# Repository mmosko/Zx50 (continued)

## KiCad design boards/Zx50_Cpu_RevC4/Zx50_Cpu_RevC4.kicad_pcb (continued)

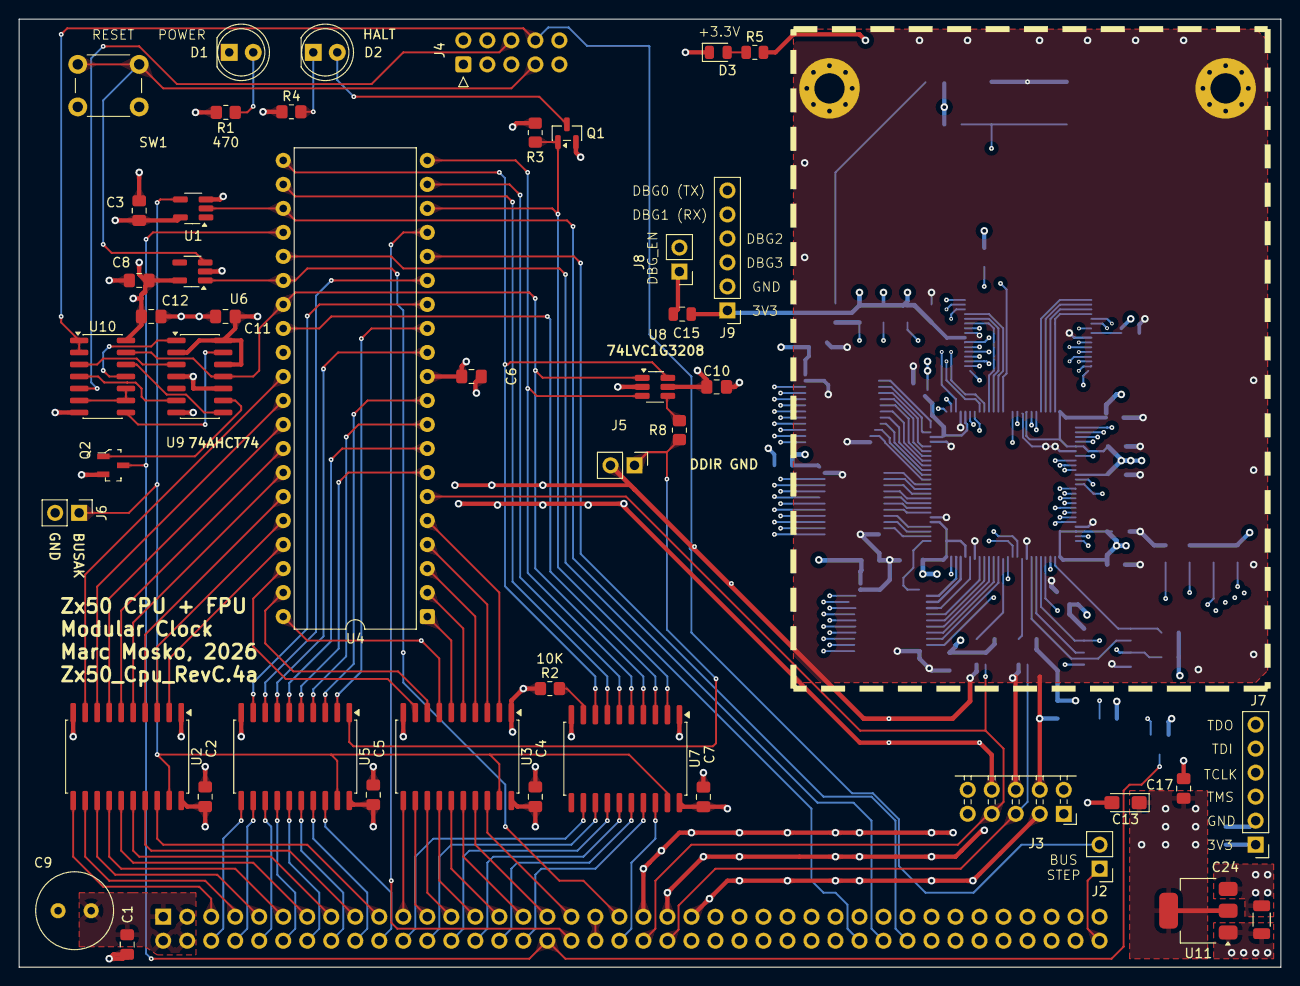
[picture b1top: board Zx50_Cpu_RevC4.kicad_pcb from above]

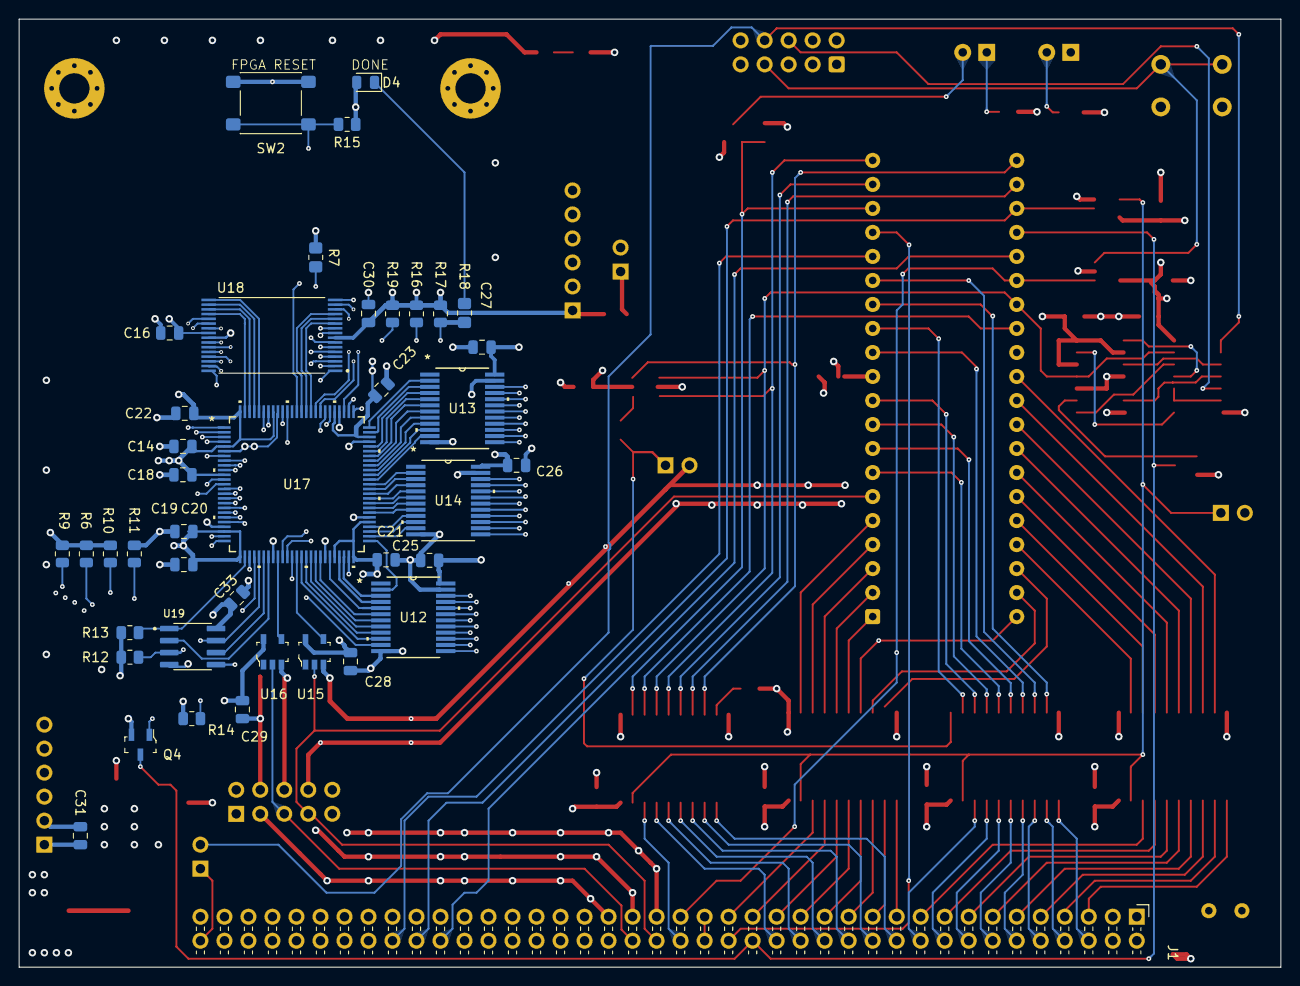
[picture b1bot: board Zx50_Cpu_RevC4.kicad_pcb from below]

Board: 6 copper layers, 133.5 x 100.3 mm, 88 parts (41 on the bottom side), 174 nets.

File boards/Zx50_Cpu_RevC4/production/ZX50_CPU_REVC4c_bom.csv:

Designator,Footprint,Quantity,Value,LCSC Part #
"C1, C10, C11, C12, C2, C3, C4, C5, C6, C7, C8",0805,11,0.1uF,C1525
C13,CP_EIA-3216-10_Kemet-I_HandSolder,1,10u,C7171
"C14, C15, C16, C18, C19, C20, C21, C22, C23, C25, C26, C27, C28, C29, C30, C31",0805,16,100nF,C28233
C17,0805,1,100n,C1525
C24,1206,1,10u,C7171
C33,0805,1,100n,C49678
C9,C_Radial_D8.0mm_H7.0mm_P3.50mm,1,100uF,
D1,LED_D5.0mm,1,PWR,
D2,LED_D5.0mm,1,HALT,
D4,0805,1,DONE,C2297
J1,PinHeader_2x40_P2.54mm_Horizontal_Edge,1,Zx50_EdgeConnector,
J2,PinHeader_1x02_P2.54mm_Vertical,1,STEP_N,
J3,PinSocket_2x05_P2.54mm_Horizontal,1,Clock Mezzanine,
J4,IDC-Header_2x05_P2.54mm_Horizontal_Edge,1,Front Panel,
J5,PinHeader_1x02_P2.54mm_Vertical,1,TP_D_DIR,
J6,PinHeader_1x02_P2.54mm_Vertical,1,TP_BUSAK,
J7,PinHeader_1x06_P2.54mm_Vertical,1,JTAG,
J8,PinHeader_1x02_P2.54mm_Vertical,1,DBG_EN,
J9,PinHeader_1x06_P2.54mm_Vertical,1,DEBUG,
Q1,SOT-23,1,BSS84,
"Q2, Q4",SOT-23-3,2,2N7002-7-F,C8545
"R1, R4",0805,2,470,C17710
"R10, R11, R15, R16, R17, R19, R6, R9",0805,8,4k7,C17713
"R12, R13, R14, R2, R7",0805,5,10k,C17414
R3,0805,1,47K,C17713
R8,0805,1,33R,C17634
SW1,SW_PUSH_6mm_H7.3mm,1,RESET,
SW2,SW_SPST_PTS645Sx43SMTR92,1,RESET,
U1,SOT-23-5_HandSoldering,1,74AHC1G14,
U10,SOIC-14_3.9x8.7mm_P1.27mm,1,74ACHT132,
U11,SOT-223-3_TabPin2,1,AMS1117-3.3,C6186
"U12, U13, U14",DB24,3,74CBTD3861,C11617
"U15, U16",SOT-753,2,74LVC1G17,C7836
U17,TQFP100_LAT,1,LCMXO2-2000HC-4TG100I,C1521620
U18,SOP50P1400X120-32N,1,IS61WV1288EEBLL-10HLI,C1349956
U19,SOIC127P600X88-8N,1,IS25LP080D-JNLE-TR,C521286
"U2, U3, U5, U7",SOIC-20W_7.5x12.8mm_P1.27mm,4,SN74ABT245BN,
U4,DIP-40_W15.24mm,1,Z84C00xxP,
U6,SOT-23-5_HandSoldering,1,MCP1316MT-46LE/OT,
U8,SOT-23-6_Handsoldering,1,74LVC1G3208,
U9,SOIC-14_3.9x8.7mm_P1.27mm,1,SN74AHCT74DRG4,

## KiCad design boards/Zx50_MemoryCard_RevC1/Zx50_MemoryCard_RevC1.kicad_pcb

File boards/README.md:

# Zx50 Project Architecture Context

## Overview

The Zx50 is a custom 8-slot, passive backplane Z80 computer. It uses a "Shadow Bus" architecture where a Raspberry Pi Pico can take over the bus via DMA (~BUSRQ / ~BUSAK) to load RAM, debug, and monitor the system.

## Core Rules & Hardware

* Backplane: 8 slots. Fully terminated with 10K SIP pull-up resistors on Address, Data, and Control lines. Includes an ~IEI/~IEO interrupt daisy chain and heavy bulk capacitance (1000µF).

* CPU: Z80 running at 8 to 10 MHz.

* Clock System: A dedicated Clock Mezzanine board that generates a 40 MHz Master Clock (MCLK) for the Pi Picos, and uses a 74HC393 to divide it down to a 10 MHz ZCLK for the Z80. It uses an async-request latch system (1G79, 1G08, 1G32) to perfectly sync the CPU clock stopping/stepping with the Pi Pico's requests, ensuring no runt pulses.

* Logic Families: * 74AHCT (specifically 74AHCT244 and 74AHCT245) are used for bus transceivers to provide the strong ±8mA current needed to drive the backplane.

* Standard 74HC / 74AHC logic is used for local onboard glue logic.

* System Reset: Handled by an MCP1316M-46LE/OT Open-Drain Supervisor IC on the CPU card. It provides a ~200ms reset timeout to allow the backplane capacitors to charge and the Pi Pico bootloaders to initialize before the Z80 wakes up.

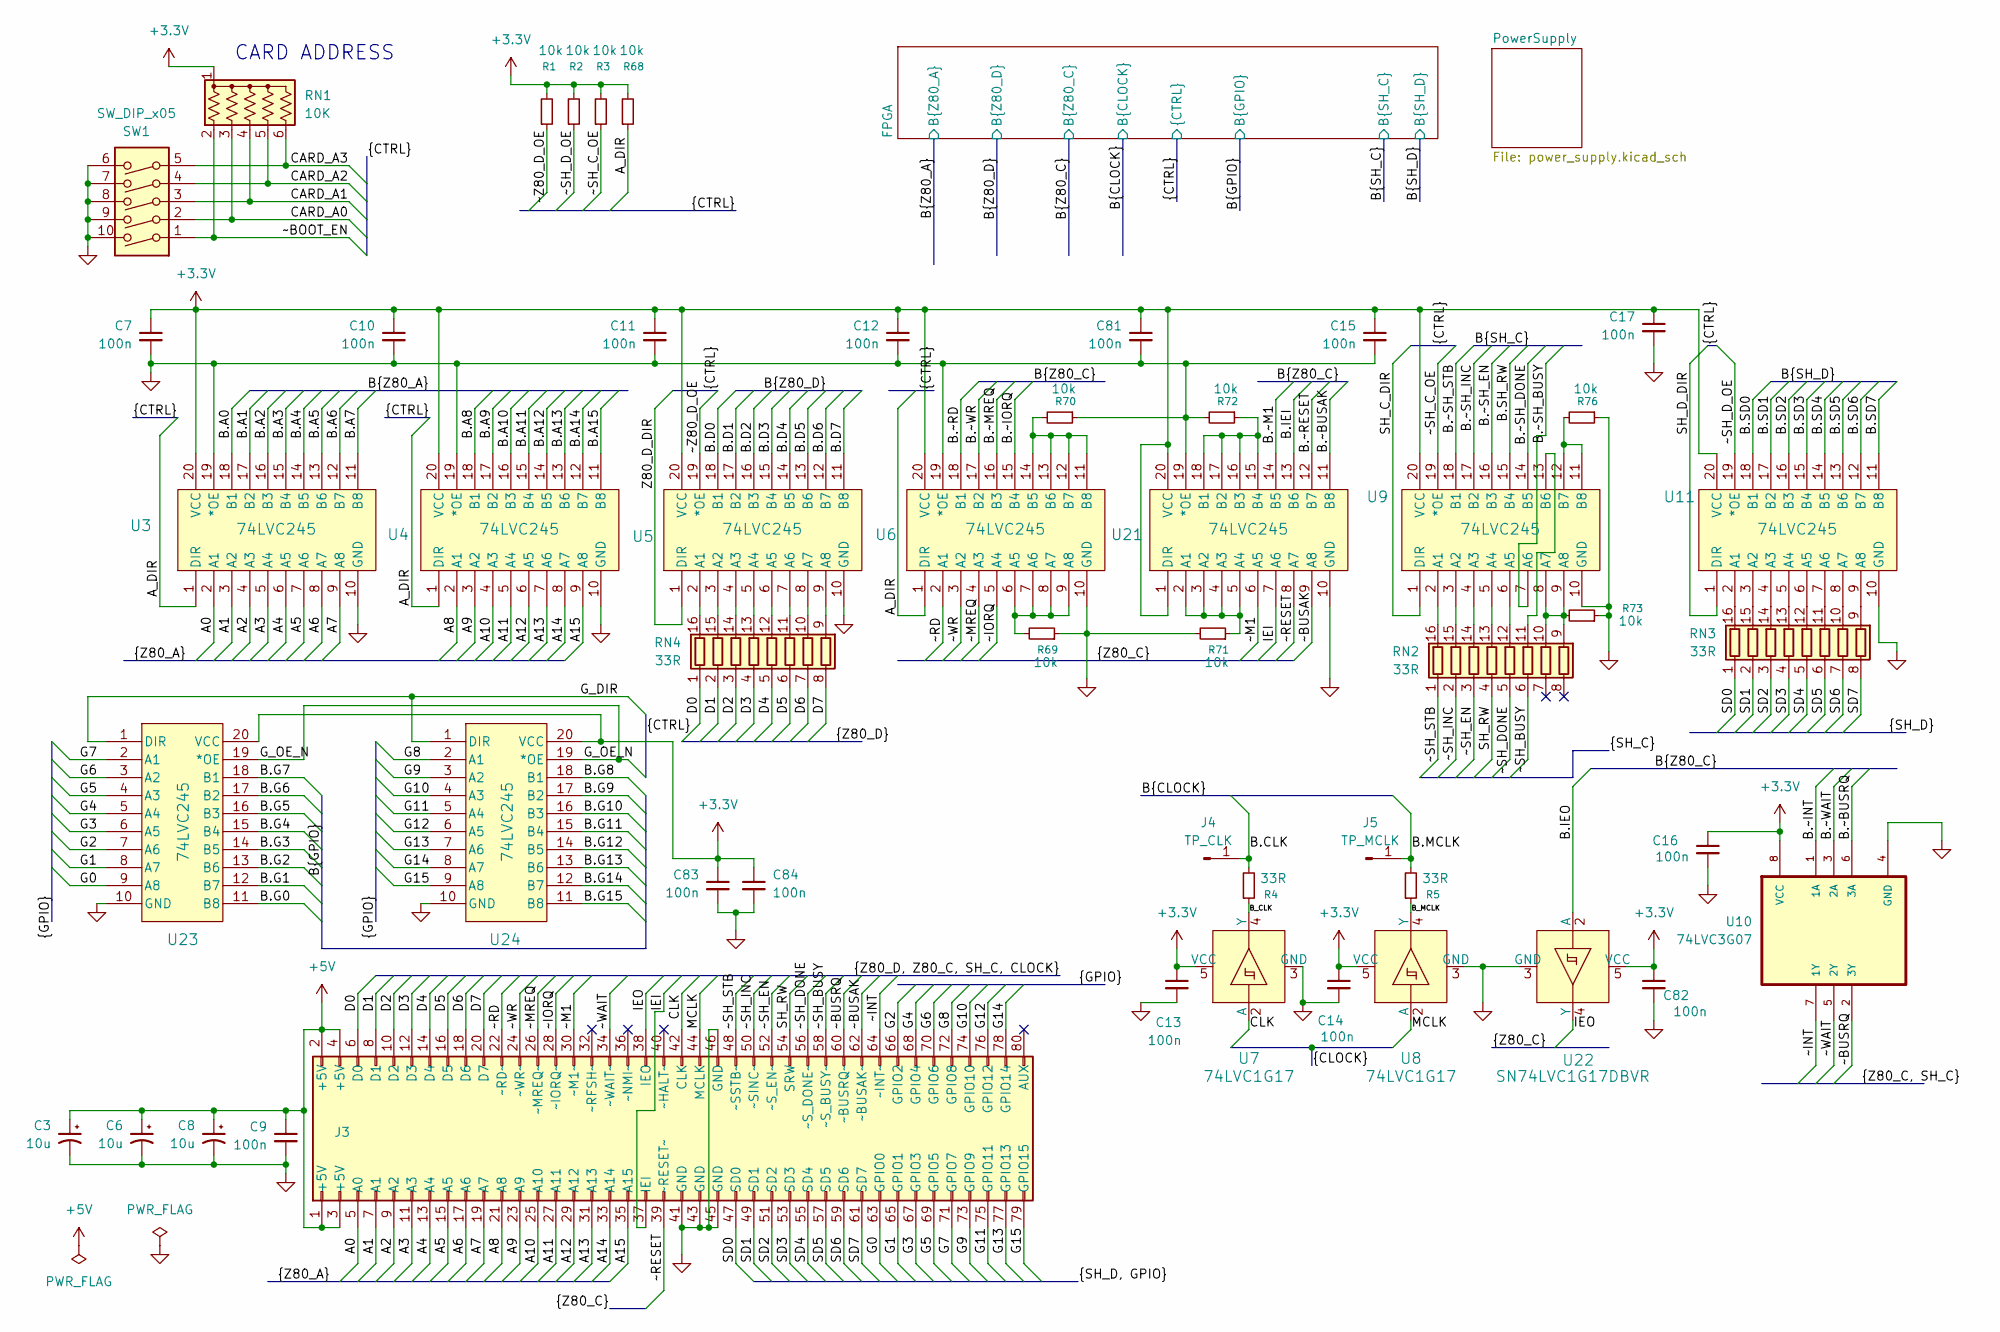
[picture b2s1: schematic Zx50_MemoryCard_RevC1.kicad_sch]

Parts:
C3, C6, C8: 10u; C_1206_3216Metric; MFG PN AVX TAJA106K016RNJ Tantalinium; LCSC C7171
C7, C9, C10, C11, C12, C13, C14, C15, C16, C17, C81, C82, C83, C84: 100n; C_0402_1005Metric; LCSC C1525
J3: Zx50_EdgeConnector; PinSocket_2x40_P2.54mm_Horizontal_Edge; DigiKey_PN 2057-PH2RA-80-UA-ND
J4: TP_CLK; PinHeader_1x01_P2.54mm_Vertical
J5: TP_MCLK; PinHeader_1x01_P2.54mm_Vertical
R1, R2, R3, R68, R69, R70, R71, R72, R73, R76: 10k; R_0805_2012Metric; MFG_PN 0805W8F1002T5E; LCSC C17414
R4, R5: 33R; R_0603_1608Metric; MFG_PN 0603WAF330JT5E; LCSC C23140
RN1: 10K; R_Array_SIP6; LCSC 4606X-AP1-103LF
RN2, RN3, RN4: 33R; R_Array_Convex_8x0602; LCSC C422182
SW1: SW_DIP_x05; SW_DIP_SPSTx05_Slide_9.78x14.88mm_W7.62mm_P2.54mm; LCSC 208-5
U3, U4, U5, U6, U9, U11, U21, U23, U24: 74LVC245; TSSOP-20_4.4x6.5mm_P0.65mm; MFG_PART SN74LVC245APWR; LCSC C7848
U7, U8: 74LVC1G17; SOT-753; MPN SN74LVC1G17DBVR; Digi-Key_PN 296-11933-1-ND
U10: 74LVC3G07; VSSOP-8_2.3x2mm_P0.5mm; MFG_PN SN74LVC3G07DCUR; LCSC C131955
U22: SN74LVC1G17DBVR; SOT-753; MPN SN74LVC1G17DBVR; Digi-Key_PN 296-11933-1-ND

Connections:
+3.3V: C7.1, C10.1, C11.1, C12.1, C13.1, C14.1, C15.1, C16.1, C17.1, C81.1, C82.1, C83.1, C84.1, R1.2, R2.2, R3.2, R68.2, RN1.1 (common), U3.20 (VCC), U4.20 (VCC), U5.20 (VCC), U6.20 (VCC), U7.5 (VCC), U8.5 (VCC), U9.20 (VCC), U10.8 (VCC), U11.20 (VCC), U21.1 (DIR), U21.20 (VCC), U22.5 (VCC), U23.20 (VCC), U24.20 (VCC); also elsewhere on the board
+5V: C3.1, C6.1, C8.1, C9.1, J3.1 (+5V), J3.2 (+5V), J3.3 (+5V), J3.4 (+5V); also elsewhere on the board
/A0: J3.5 (A0), U3.2 (A1)
/A1: J3.7 (A1), U3.3 (A2)
/A2: J3.9 (A2), U3.4 (A3)
/A3: J3.11 (A3), U3.5 (A4)
/A4: J3.13 (A4), U3.6 (A5)
/A5: J3.15 (A5), U3.7 (A6)
/A6: J3.17 (A6), U3.8 (A7)
/A7: J3.19 (A7), U3.9 (A8)
/A8: J3.21 (A8), U4.2 (A1)
/A9: J3.23 (A9), U4.3 (A2)
/A10: J3.25 (A10), U4.4 (A3)
/A11: J3.27 (A11), U4.5 (A4)
/A12: J3.29 (A12), U4.6 (A5)
/A13: J3.31 (A13), U4.7 (A6)
/A14: J3.33 (A14), U4.8 (A7)
/A15: J3.35 (A15), U4.9 (A8)
/A_DIR: R68.1, U3.1 (DIR), U4.1 (DIR), U6.1 (DIR); also elsewhere on the board
/B.A0: U3.18 (B1); also elsewhere on the board
/B.A1: U3.17 (B2); also elsewhere on the board
/B.A2: U3.16 (B3); also elsewhere on the board
/B.A3: U3.15 (B4); also elsewhere on the board
/B.A4: U3.14 (B5); also elsewhere on the board
/B.A5: U3.13 (B6); also elsewhere on the board
/B.A6: U3.12 (B7); also elsewhere on the board
/B.A7: U3.11 (B8); also elsewhere on the board
/B.A8: U4.18 (B1); also elsewhere on the board
/B.A9: U4.17 (B2); also elsewhere on the board
/B.A10: U4.16 (B3); also elsewhere on the board
/B.A11: U4.15 (B4); also elsewhere on the board
/B.A12: U4.14 (B5); also elsewhere on the board
/B.A13: U4.13 (B6); also elsewhere on the board
/B.A14: U4.12 (B7); also elsewhere on the board
/B.A15: U4.11 (B8); also elsewhere on the board
/B.CLK: J4.1, R4.2; also elsewhere on the board
/B.D0: U5.18 (B1); also elsewhere on the board
/B.D1: U5.17 (B2); also elsewhere on the board
/B.D2: U5.16 (B3); also elsewhere on the board
/B.D3: U5.15 (B4); also elsewhere on the board
/B.D4: U5.14 (B5); also elsewhere on the board
/B.D5: U5.13 (B6); also elsewhere on the board
/B.D6: U5.12 (B7); also elsewhere on the board
/B.D7: U5.11 (B8); also elsewhere on the board
/B.G0: U23.11 (B8); also elsewhere on the board
/B.G1: U23.12 (B7); also elsewhere on the board
/B.G2: U23.13 (B6); also elsewhere on the board
/B.G3: U23.14 (B5); also elsewhere on the board
/B.G4: U23.15 (B4); also elsewhere on the board
/B.G5: U23.16 (B3); also elsewhere on the board
/B.G6: U23.17 (B2); also elsewhere on the board
/B.G7: U23.18 (B1); also elsewhere on the board
/B.G8: U24.18 (B1); also elsewhere on the board
/B.G9: U24.17 (B2); also elsewhere on the board
/B.G10: U24.16 (B3); also elsewhere on the board
/B.G11: U24.15 (B4); also elsewhere on the board
/B.G12: U24.14 (B5); also elsewhere on the board
/B.G13: U24.13 (B6); also elsewhere on the board
/B.G14: U24.12 (B7); also elsewhere on the board
/B.G15: U24.11 (B8); also elsewhere on the board
/B.IEI: U21.13 (B6); also elsewhere on the board
/B.IEO: U22.2 (A); also elsewhere on the board
/B.MCLK: J5.1, R5.2; also elsewhere on the board
/B.SD0: U11.18 (B1); also elsewhere on the board
/B.SD1: U11.17 (B2); also elsewhere on the board
/B.SD2: U11.16 (B3); also elsewhere on the board
/B.SD3: U11.15 (B4); also elsewhere on the board
/B.SD4: U11.14 (B5); also elsewhere on the board
/B.SD5: U11.13 (B6); also elsewhere on the board
/B.SD6: U11.12 (B7); also elsewhere on the board
/B.SD7: U11.11 (B8); also elsewhere on the board
/B.SH_RW: U9.15 (B4); also elsewhere on the board
/B.~BUSAK: U21.11 (B8); also elsewhere on the board
/B.~BUSRQ: U10.6 (3A); also elsewhere on the board
/B.~INT: U10.1 (1A); also elsewhere on the board
/B.~IORQ: U6.15 (B4); also elsewhere on the board
/B.~M1: U21.14 (B5); also elsewhere on the board
/B.~MREQ: U6.16 (B3); also elsewhere on the board
/B.~RD: U6.18 (B1); also elsewhere on the board
/B.~RESET: U21.12 (B7); also elsewhere on the board
/B.~SH_BUSY: U9.7 (A6); also elsewhere on the board
/B.~SH_DONE: U9.14 (B5); also elsewhere on the board
/B.~SH_EN: U9.16 (B3); also elsewhere on the board
/B.~SH_INC: U9.17 (B2); also elsewhere on the board
/B.~SH_STB: U9.18 (B1); also elsewhere on the board
/B.~WAIT: U10.3 (2A); also elsewhere on the board
/B.~WR: U6.17 (B2); also elsewhere on the board
/B_CLK: R4.1, U7.4 (Y)
/B_MCLK: R5.1, U8.4 (Y)
/CARD_A0: RN1.3 (R2), SW1.2; also elsewhere on the board
/CARD_A1: RN1.4 (R3), SW1.3; also elsewhere on the board
/CARD_A2: RN1.5 (R4), SW1.4; also elsewhere on the board
/CARD_A3: RN1.6 (R5), SW1.5; also elsewhere on the board
/CLK: J3.42 (CLK), U7.2 (A)
/D0: J3.6 (D0), RN4.1 (R1.1)
/D1: J3.8 (D1), RN4.2 (R2.1)
/D2: J3.10 (D2), RN4.3 (R3.1)
/D3: J3.12 (D3), RN4.4 (R4.1)
/D4: J3.14 (D4), RN4.5 (R5.1)
/D5: J3.16 (D5), RN4.6 (R6.1)
/D6: J3.18 (D6), RN4.7 (R7.1)
/D7: J3.20 (D7), RN4.8 (R8.1)
/G0: J3.63 (GPIO0), U23.9 (A8)
/G1: J3.65 (GPIO1), U23.8 (A7)
/G2: J3.66 (GPIO2), U23.7 (A6)
/G3: J3.67 (GPIO3), U23.6 (A5)
/G4: J3.68 (GPIO4), U23.5 (A4)
/G5: J3.69 (GPIO5), U23.4 (A3)
/G6: J3.70 (GPIO6), U23.3 (A2)
/G7: J3.71 (GPIO7), U23.2 (A1)
/G8: J3.72 (GPIO8), U24.2 (A1)
/G9: J3.73 (GPIO9), U24.3 (A2)
/G10: J3.74 (GPIO10), U24.4 (A3)
/G11: J3.75 (GPIO11), U24.5 (A4)
/G12: J3.76 (GPIO12), U24.6 (A5)
/G13: J3.77 (GPIO13), U24.7 (A6)
/G14: J3.78 (GPIO14), U24.8 (A7)
/G15: J3.79 (GPIO15), U24.9 (A8)
/G_DIR: U23.1 (DIR), U24.1 (DIR); also elsewhere on the board
/G_OE_N: U23.19 (*OE), U24.19 (*OE); also elsewhere on the board
/IEI: J3.37 (IEI), U21.7 (A6)
/IEO: J3.38 (IEO), U22.4 (Y)
/MCLK: J3.44 (MCLK), U8.2 (A)
/SD0: J3.47 (SD0), RN3.1 (R1.1)
/SD1: J3.49 (SD1), RN3.2 (R2.1)
/SD2: J3.51 (SD2), RN3.3 (R3.1)
/SD3: J3.53 (SD3), RN3.4 (R4.1)
/SD4: J3.55 (SD4), RN3.5 (R5.1)
/SD5: J3.57 (SD5), RN3.6 (R6.1)
/SD6: J3.59 (SD6), RN3.7 (R7.1)
/SD7: J3.61 (SD7), RN3.8 (R8.1)
/SH_C_DIR: U9.1 (DIR); also elsewhere on the board
/SH_D_DIR: U11.1 (DIR); also elsewhere on the board
/SH_RW: J3.54 (SRW), RN2.4 (R4.1)
/Z80_D_DIR: U5.1 (DIR); also elsewhere on the board
/~BOOT_EN: RN1.2 (R1), SW1.1; also elsewhere on the board
/~BUSAK: J3.62 (~BUSAK~), U21.9 (A8)
/~BUSRQ: J3.60 (~BUSRQ~), U10.2 (3Y)
/~INT: J3.64 (~INT~), U10.7 (1Y)
/~IORQ: J3.28 (~IORQ~), U6.5 (A4)
/~M1: J3.30 (~M1~), U21.6 (A5)
/~MREQ: J3.26 (~MREQ~), U6.4 (A3)
/~RD: J3.22 (~RD~), U6.2 (A1)
/~RESET: J3.39 (~RESET~), U21.8 (A7)
/~SH_BUSY: J3.58 (~S_BUSY~), RN2.6 (R6.1)
/~SH_C_OE: R3.1, U9.19 (*OE); also elsewhere on the board
/~SH_DONE: J3.56 (~S_DONE~), RN2.5 (R5.1)
/~SH_D_OE: R2.1, U11.19 (*OE); also elsewhere on the board
/~SH_EN: J3.52 (~S_EN~), RN2.3 (R3.1)
/~SH_INC: J3.50 (~SINC~), RN2.2 (R2.1)
/~SH_STB: J3.48 (~SSTB~), RN2.1 (R1.1)
/~WAIT: J3.34 (~WAIT~), U10.5 (2Y)
/~WR: J3.24 (~WR~), U6.3 (A2)
/~Z80_D_OE: R1.1, U5.19 (*OE); also elsewhere on the board
GND: C3.2, C6.2, C7.2, C8.2, C9.2, C10.2, C11.2, C12.2, C13.2, C14.2, C15.2, C16.2, C17.2, C81.2, C82.2, C83.2, C84.2, J3.41 (GND), J3.43 (GND), J3.45 (GND), J3.46 (GND), R69.1, R70.1, R71.2, R72.2, R73.1, R76.1, SW1.6, SW1.7, SW1.8, SW1.9, SW1.10, U3.10 (GND), U3.19 (*OE), U4.10 (GND), U4.19 (*OE), U5.10 (GND), U6.10 (GND), U6.19 (*OE), U7.3 (GND), U8.3 (GND), U9.10 (GND), U10.4 (GND), U11.10 (GND), U21.10 (GND), U21.19 (*OE), U22.3 (GND), U23.10 (GND), U24.10 (GND); also elsewhere on the board
unnamed: RN2.16 (R1.2), U9.2 (A1)
unnamed: RN2.15 (R2.2), U9.3 (A2)
unnamed: RN2.14 (R3.2), U9.4 (A3)
unnamed: RN2.13 (R4.2), U9.5 (A4)
unnamed: RN2.12 (R5.2), U9.6 (A5)
unnamed: RN2.11 (R6.2), U9.13 (B6)
unnamed: R73.2, RN2.9 (R8.2), RN2.10 (R7.2), U9.8 (A7), U9.9 (A8)
unnamed: RN3.16 (R1.2), U11.2 (A1)
unnamed: RN3.15 (R2.2), U11.3 (A2)
unnamed: RN3.14 (R3.2), U11.4 (A3)
unnamed: RN3.13 (R4.2), U11.5 (A4)
unnamed: RN3.12 (R5.2), U11.6 (A5)
unnamed: RN3.11 (R6.2), U11.7 (A6)
unnamed: RN3.10 (R7.2), U11.8 (A7)
unnamed: RN3.9 (R8.2), U11.9 (A8)
unnamed: RN4.16 (R1.2), U5.2 (A1)
unnamed: RN4.15 (R2.2), U5.3 (A2)
unnamed: RN4.14 (R3.2), U5.4 (A3)
unnamed: RN4.13 (R4.2), U5.5 (A4)
unnamed: RN4.12 (R5.2), U5.6 (A5)
unnamed: RN4.11 (R6.2), U5.7 (A6)
unnamed: RN4.10 (R7.2), U5.8 (A7)
unnamed: RN4.9 (R8.2), U5.9 (A8)
unnamed: R69.2, U6.6 (A5), U6.7 (A6), U6.8 (A7), U6.9 (A8)
unnamed: R70.2, U6.11 (B8), U6.12 (B7), U6.13 (B6), U6.14 (B5)
unnamed: R76.2, U9.11 (B8), U9.12 (B7)
unnamed: R71.1, U21.2 (A1), U21.3 (A2), U21.4 (A3), U21.5 (A4)
unnamed: R72.1, U21.15 (B4), U21.16 (B3), U21.17 (B2), U21.18 (B1)

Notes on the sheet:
CARD ADDRESS

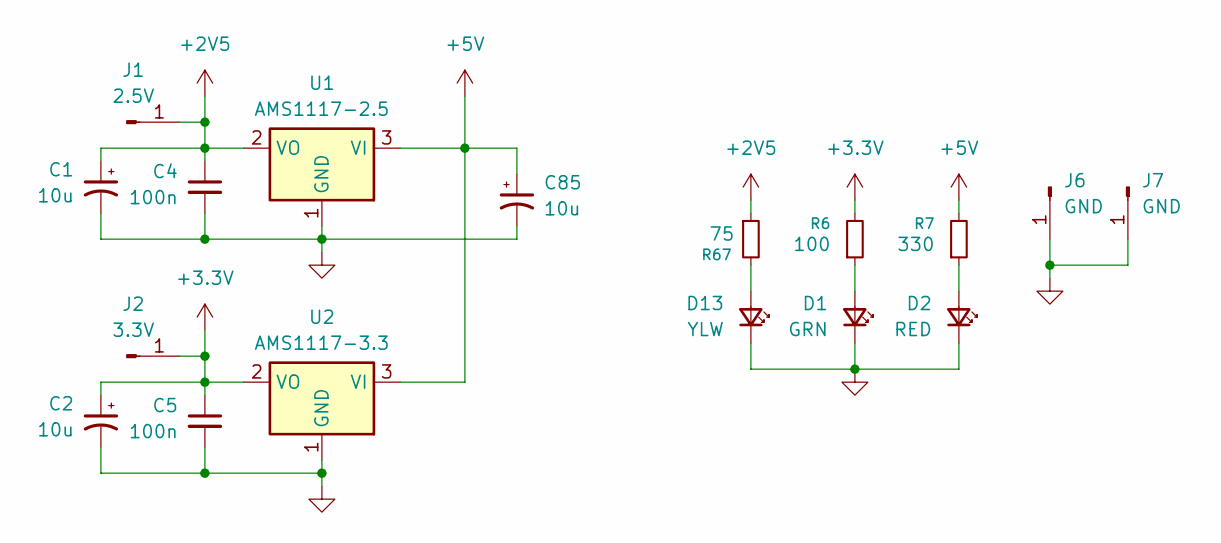
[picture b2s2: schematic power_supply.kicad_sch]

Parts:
C1, C2, C85: 10u; C_1206_3216Metric; MFG PN AVX TAJA106K016RNJ Tantalinium; LCSC C7171
C4, C5: 100n; C_0402_1005Metric; LCSC C1525
D1: GRN; LED_0805_2012Metric; MFG_PN KT-0805G; LCSC C2297
D2: RED; LED_0805_2012Metric; MFG_PN NCD0805R1; LCSC C84256
D13: YLW; LED_0805_2012Metric; MFG_PN KT-0805G; LCSC C2297
J1: 2.5V; PinHeader_1x01_P2.54mm_Vertical
J2: 3.3V; PinHeader_1x01_P2.54mm_Vertical
J6, J7: GND; PinHeader_1x01_P2.54mm_Vertical
R6: 100; R_0805_2012Metric; MFG_PN 0805W8F1000T5E; LCSC C17408
R7: 330; R_0805_2012Metric; MFG_PN 0805W8F3300T5E; LCSC C17630
R67: 75; R_0603_1608Metric; MFG_PN 0603WAF750JT5E; LCSC C4275
U1: AMS1117-2.5; SOT-223-3_TabPin2; Mouser_PN 926-LM1117MPX2.5NOPB
U2: AMS1117-3.3; SOT-223-3_TabPin2; Mouser_PN 926-LM1117MPX3.3NOPB

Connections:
+2V5: C1.1, C4.1, J1.1, R67.1, U1.2 (VO); also elsewhere on the board
+3.3V: C2.1, C5.1, J2.1, R6.2, U2.2 (VO); also elsewhere on the board
+5V: C85.1, R7.2, U1.3 (VI), U2.3 (VI); also elsewhere on the board
GND: C1.2, C2.2, C4.2, C5.2, C85.2, D1.1 (K), D2.1 (K), D13.1 (K), J6.1, J7.1, U1.1 (GND), U2.1 (GND); also elsewhere on the board
unnamed: D1.2 (A), R6.1
unnamed: D2.2 (A), R7.1
unnamed: D13.2 (A), R67.2
